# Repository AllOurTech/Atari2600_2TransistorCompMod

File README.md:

# Atari2600 Two Transistor Comp Mod
A PCB design for a two transistor based composit video out mod the the Atari 2600.

The schematic is based on the one found in [this](https://forums.atariage.com/topic/271678-simple-diy-composite-video-mod/) post on the Atari Age forums.

Gerber files have been generated and can be found in the [Gerbers folder](./Gerbers) including a zip file to be sent to your favorite PCB fab house.
<br>
There is also a interactive BOM file in the [bom folder](./bom)

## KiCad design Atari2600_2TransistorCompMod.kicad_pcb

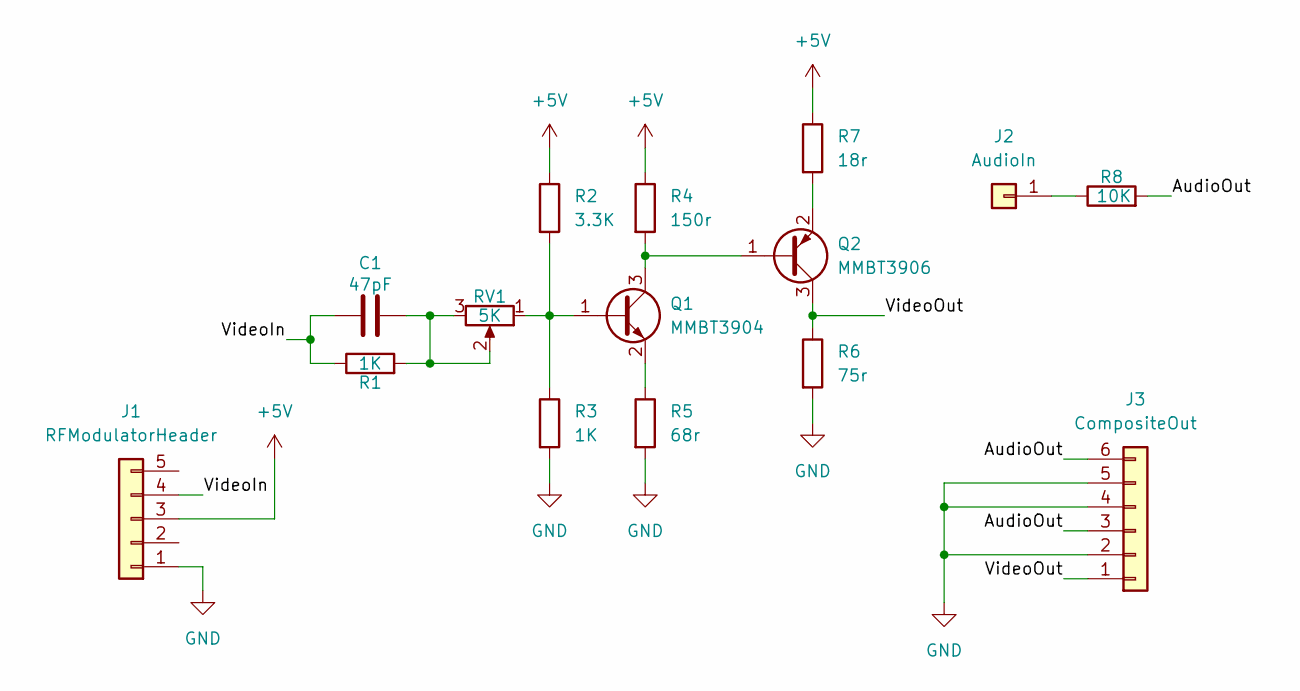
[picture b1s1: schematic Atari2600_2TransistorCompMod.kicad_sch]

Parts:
C1: 47pF; C_0603_1608Metric
J1: RFModulatorHeader; PinHeader_1x05_P2.54mm_Horizontal
J2: AudioIn; PinHeader_1x01_P2.54mm_Vertical
J3: CompositeOut; PinHeader_1x06_P2.54mm_Vertical
Q1: MMBT3904; SOT-23
Q2: MMBT3906; SOT-23
R1, R3: 1K; R_0603_1608Metric
R2: 3.3K; R_0603_1608Metric
R4: 150r; R_0603_1608Metric
R5: 68r; R_0603_1608Metric
R6: 75r; R_0603_1608Metric
R7: 18r; R_0603_1608Metric
R8: 10K; R_0603_1608Metric
RV1: 5K; Potentiometer_Vishay_T73YP_Vertical

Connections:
+5V: J1.3, R2.1, R4.1, R7.1
/AudioOut: J3.3, J3.6, R8.2
/VideoIn: C1.1, J1.4, R1.1
/VideoOut: J3.1, Q2.3 (C), R6.1
GND: J1.1, J3.2, J3.4, J3.5, R3.2, R5.2, R6.2
unnamed: C1.2, R1.2, RV1.2, RV1.3
unnamed: J2.1, R8.1
unnamed: Q1.1 (B), R2.2, R3.1, RV1.1
unnamed: Q1.3 (C), Q2.1 (B), R4.2
unnamed: Q1.2 (E), R5.1
unnamed: Q2.2 (E), R7.2

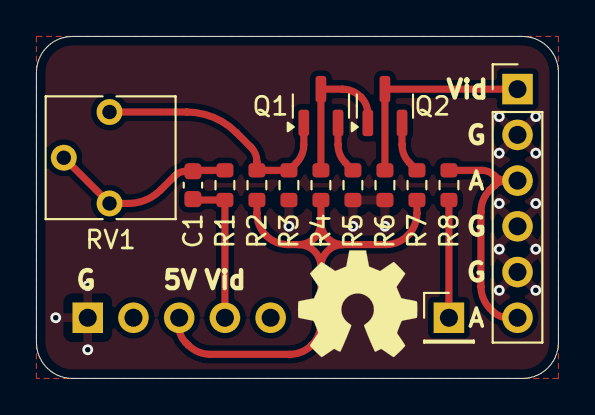
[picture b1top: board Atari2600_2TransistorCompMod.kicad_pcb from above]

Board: 2 copper layers, 29.0 x 19.0 mm, 15 parts (1 on the bottom side), 11 nets.

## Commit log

2025-09-19 Update README.md
    Updated readme
2025-09-19 Update LICENSE
2025-09-19 Create LICENSE
    Added an open hardware license
2025-09-20 Added PCB render image to README.
2025-09-20 Added gerbers and iBOM
2025-10-08 Update README.md
    Added link to original Atari Age forum post containing the schematic.
